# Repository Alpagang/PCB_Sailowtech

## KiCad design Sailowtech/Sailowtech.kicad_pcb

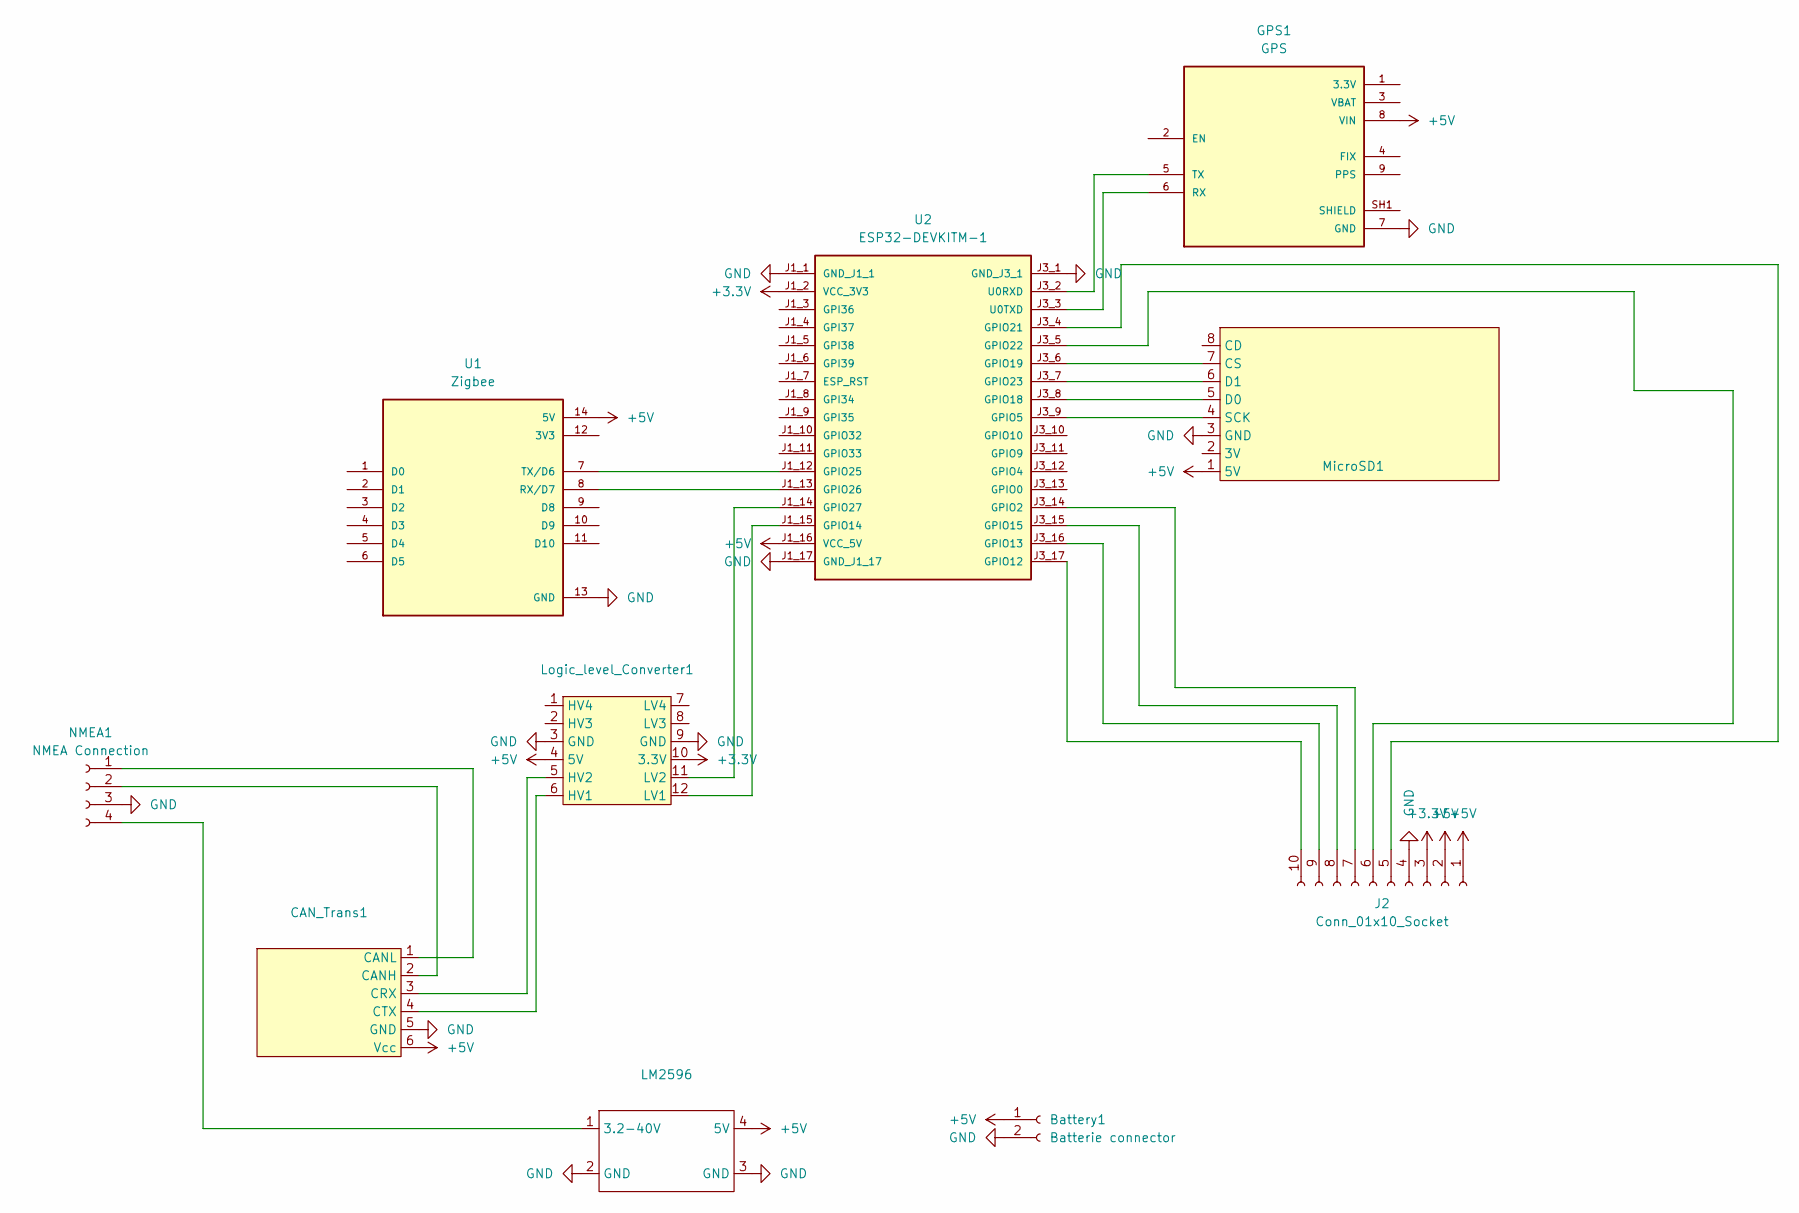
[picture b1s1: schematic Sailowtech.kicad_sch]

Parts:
Battery1: Batterie connector; PhoenixContact_MCV_1,5_2-G-3.5_1x02_P3.50mm_Vertical
CAN_Trans1: MCP - Canbus
GPS1: GPS; XCVR_746; PARTREV 2022-12-01; DigiKey_Part_Number 1528-1153-ND
J2: Conn_01x10_Socket; PinHeader_1x10_P2.54mm_Vertical
LM2596: Transformer 16V to 5V
Logic_level_Converter1: Logic_level_converter
MicroSD1: SD Card holder
NMEA1: NMEA Connection; PhoenixContact_MCV_1,5_4-G-3.5_1x04_P3.50mm_Vertical
U1: Zigbee; MODULE_113991254; PARTREV v1.0; DigiKey_Part_Number 1597-113991254-ND
U2: ESP32-DEVKITM-1; MODULE_ESP32-DEVKITM-1; PARTREV 1.0; DigiKey_Part_Number 1965-ESP32-DEVKITM-1-ND

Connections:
+3.3V: J2.3, Logic_level_Converter1.10 (3.3V), U2.J1_2 (VCC_3V3)
+5V: Battery1.1, CAN_Trans1.6 (Vcc), GPS1.8 (VIN), J2.1, J2.2, LM2596.4 (5V), Logic_level_Converter1.4 (5V), MicroSD1.1 (5V), U1.14 (5V), U2.J1_16 (VCC_5V)
GND: Battery1.2, CAN_Trans1.5 (GND), GPS1.7 (GND), J2.4, LM2596.2 (GND), LM2596.3 (GND), Logic_level_Converter1.3 (GND), Logic_level_Converter1.9 (GND), MicroSD1.3 (GND), NMEA1.3, U1.13 (GND), U2.J1_1 (GND_J1_1), U2.J1_17 (GND_J1_17), U2.J3_1 (GND_J3_1)
unnamed: CAN_Trans1.2 (CANH), NMEA1.2
unnamed: CAN_Trans1.1 (CANL), NMEA1.1
unnamed: CAN_Trans1.3 (CRX), Logic_level_Converter1.5 (HV2)
unnamed: CAN_Trans1.4 (CTX), Logic_level_Converter1.6 (HV1)
unnamed: GPS1.6 (RX), U2.J3_3 (U0TXD)
unnamed: GPS1.SH1 (SHIELD), GPS1.SH2 (SHIELD)
unnamed: GPS1.5 (TX), U2.J3_2 (U0RXD)
unnamed: J2.5, U2.J3_4 (GPIO21)
unnamed: J2.6, U2.J3_5 (GPIO22)
unnamed: J2.7, U2.J3_14 (GPIO2)
unnamed: J2.8, U2.J3_15 (GPIO15)
unnamed: J2.9, U2.J3_16 (GPIO13)
unnamed: J2.10, U2.J3_17 (GPIO12)
unnamed: LM2596.1 (3.2-40V), NMEA1.4
unnamed: Logic_level_Converter1.12 (LV1), U2.J1_15 (GPIO14)
unnamed: Logic_level_Converter1.11 (LV2), U2.J1_14 (GPIO27)
unnamed: MicroSD1.7 (CS), U2.J3_6 (GPIO19)
unnamed: MicroSD1.5 (D0), U2.J3_8 (GPIO18)
unnamed: MicroSD1.6 (D1), U2.J3_7 (GPIO23)
unnamed: MicroSD1.4 (SCK), U2.J3_9 (GPIO5)
unnamed: U1.8 (RX/D7), U2.J1_13 (GPIO26)
unnamed: U1.7 (TX/D6), U2.J1_12 (GPIO25)

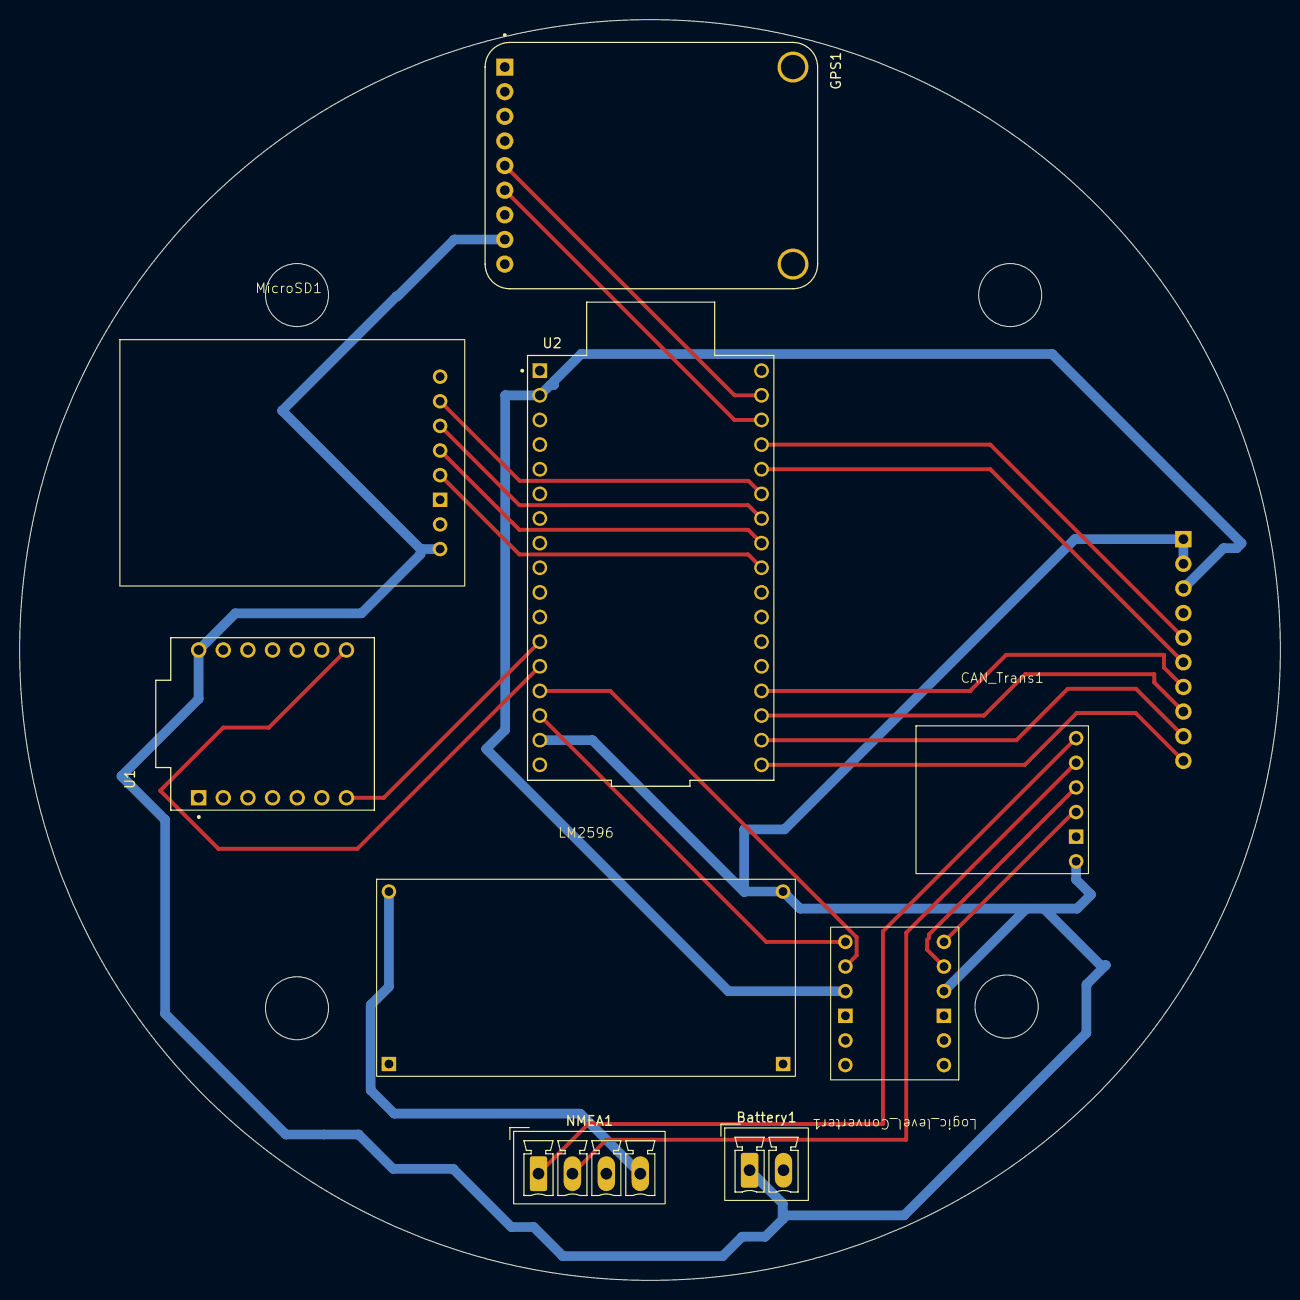
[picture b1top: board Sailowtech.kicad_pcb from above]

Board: 2 copper layers, 130.0 x 130.0 mm, 10 parts (1 on the bottom side), 25 nets.

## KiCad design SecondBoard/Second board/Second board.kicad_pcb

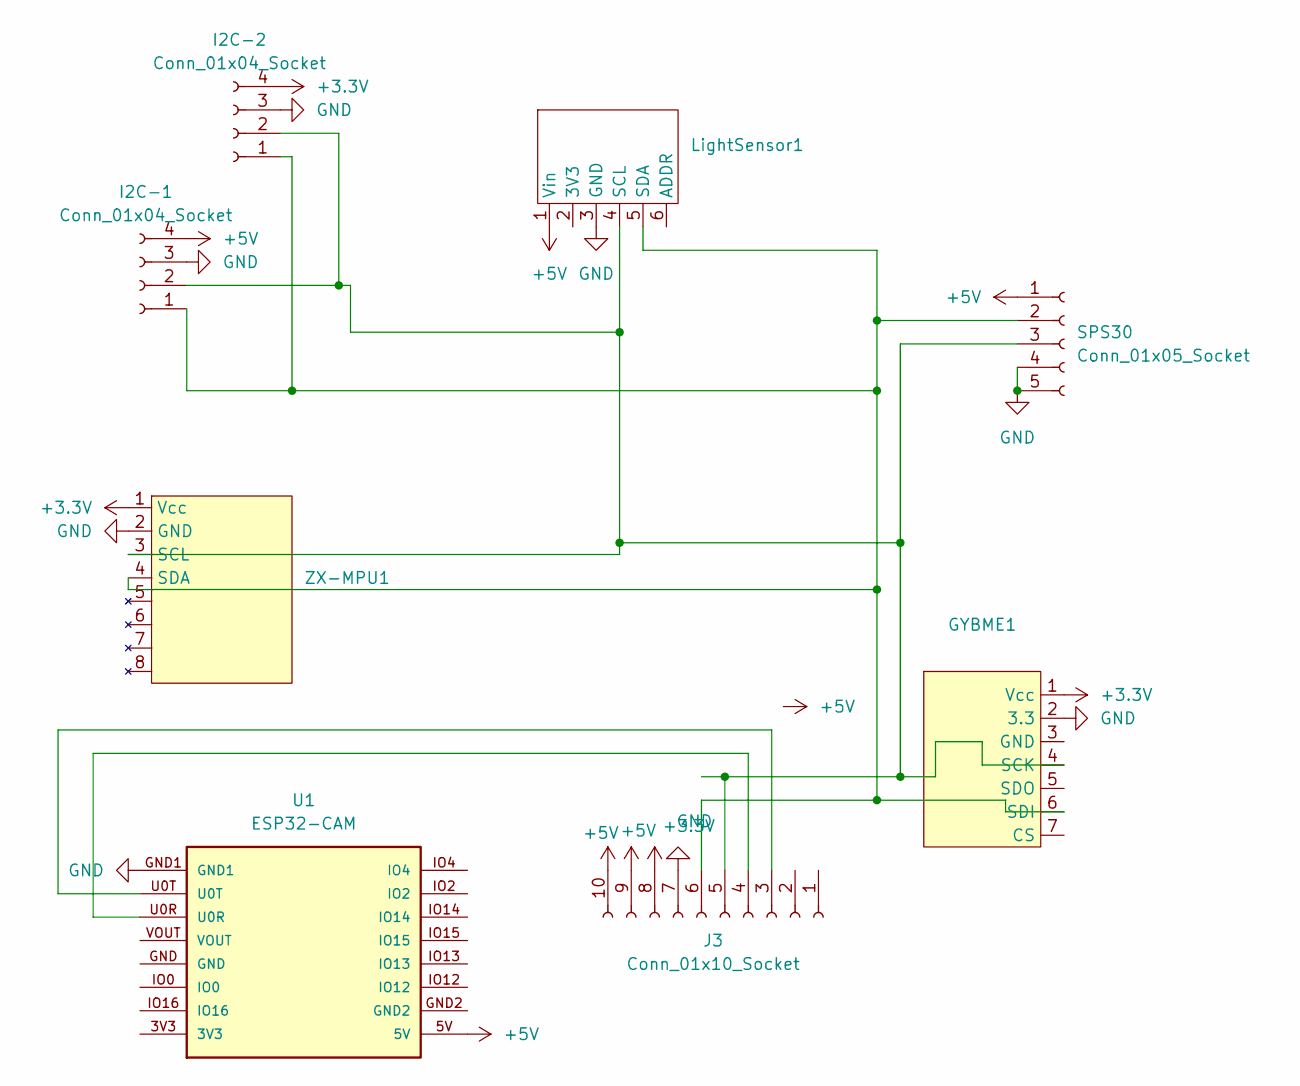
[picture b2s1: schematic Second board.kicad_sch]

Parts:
GYBME1: Sans titre
I2C-1, I2C-2: Conn_01x04_Socket; JST_XH_B4B-XH-AM_1x04_P2.50mm_Vertical
J3: Conn_01x10_Socket; PinSocket_1x10_P2.54mm_Vertical
LightSensor1: BH1750
SPS30: Conn_01x05_Socket; TerminalBlock_Phoenix_MKDS-1,5-5_1x05_P5.00mm_Horizontal
U1: ESP32-CAM
ZX-MPU1: ZX-MPU6050

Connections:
+3.3V: GYBME1.1 (Vcc), I2C-2.4, J3.8, ZX-MPU1.1 (Vcc)
+5V: I2C-1.4, J3.9, J3.10, LightSensor1.1 (Vin), SPS30.1, U1.5V
GND: GYBME1.2 (3.3), I2C-1.3, I2C-2.3, J3.7, LightSensor1.3 (GND), SPS30.4, SPS30.5, U1.GND1, ZX-MPU1.2 (GND)
unnamed: GYBME1.4 (SCK), I2C-1.2, I2C-2.2, J3.5, LightSensor1.4 (SCL), SPS30.3, ZX-MPU1.3 (SCL)
unnamed: GYBME1.6 (SDI), I2C-1.1, I2C-2.1, J3.6, LightSensor1.5 (SDA), SPS30.2, ZX-MPU1.4 (SDA)
unnamed: J3.3, U1.U0T
unnamed: J3.4, U1.U0R

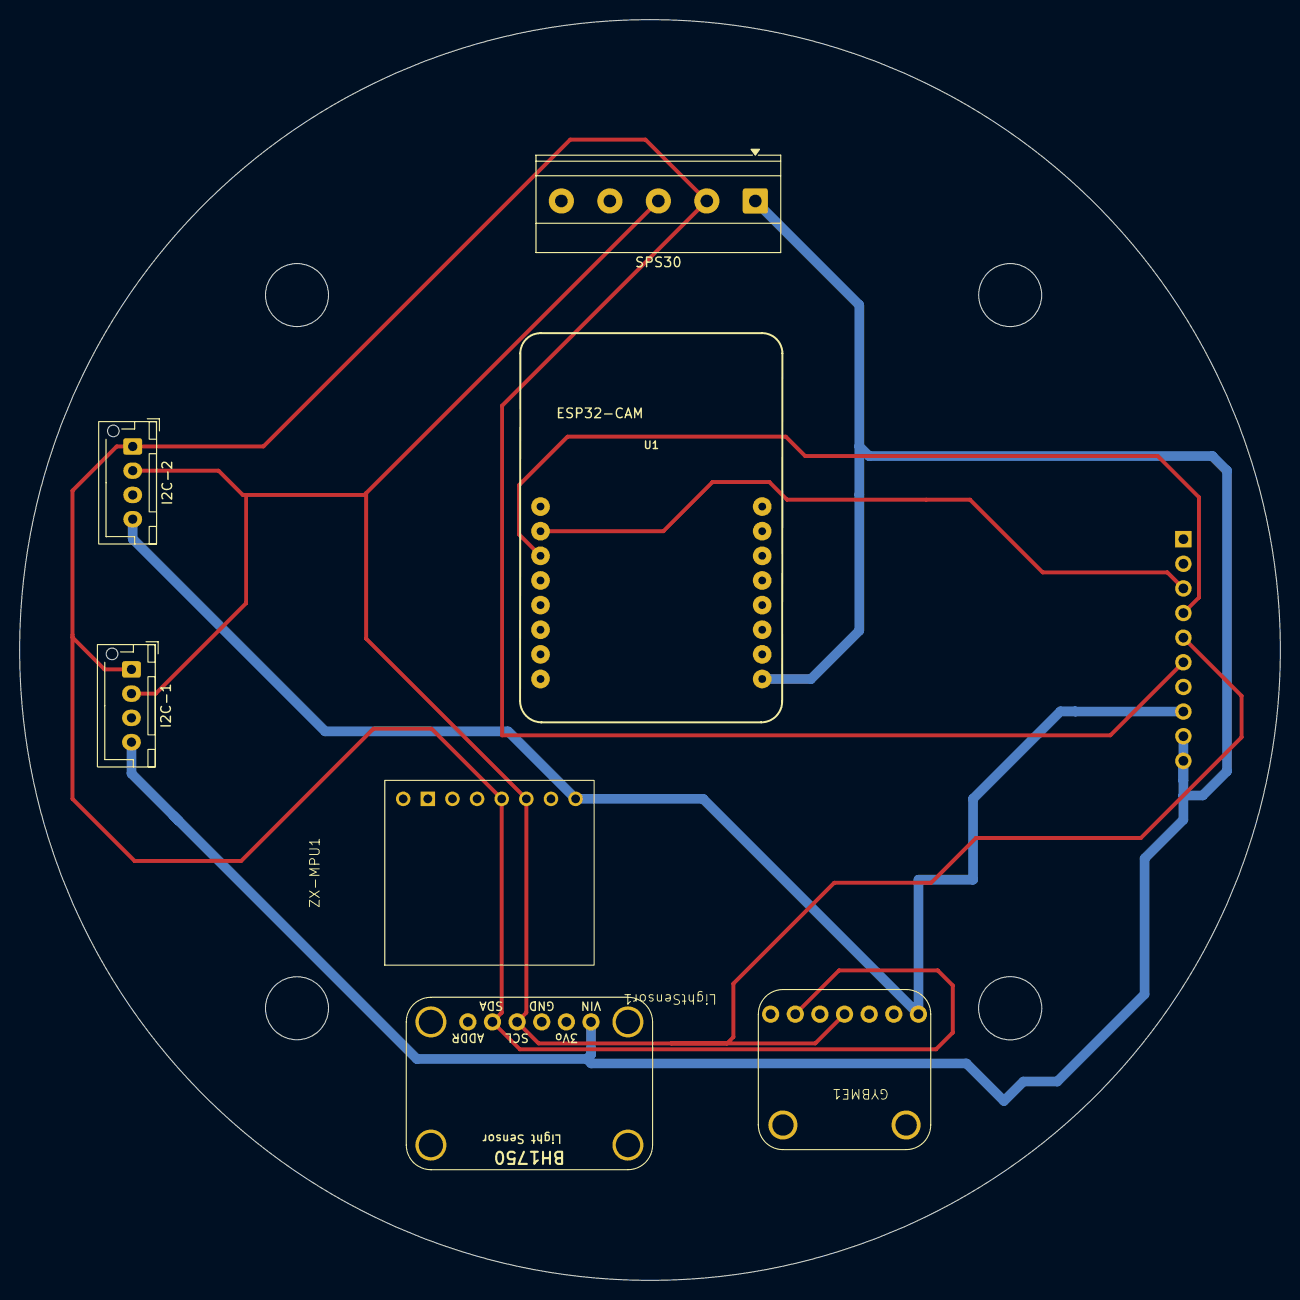
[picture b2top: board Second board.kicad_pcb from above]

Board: 2 copper layers, 130.0 x 130.0 mm, 8 parts (1 on the bottom side), 7 nets.

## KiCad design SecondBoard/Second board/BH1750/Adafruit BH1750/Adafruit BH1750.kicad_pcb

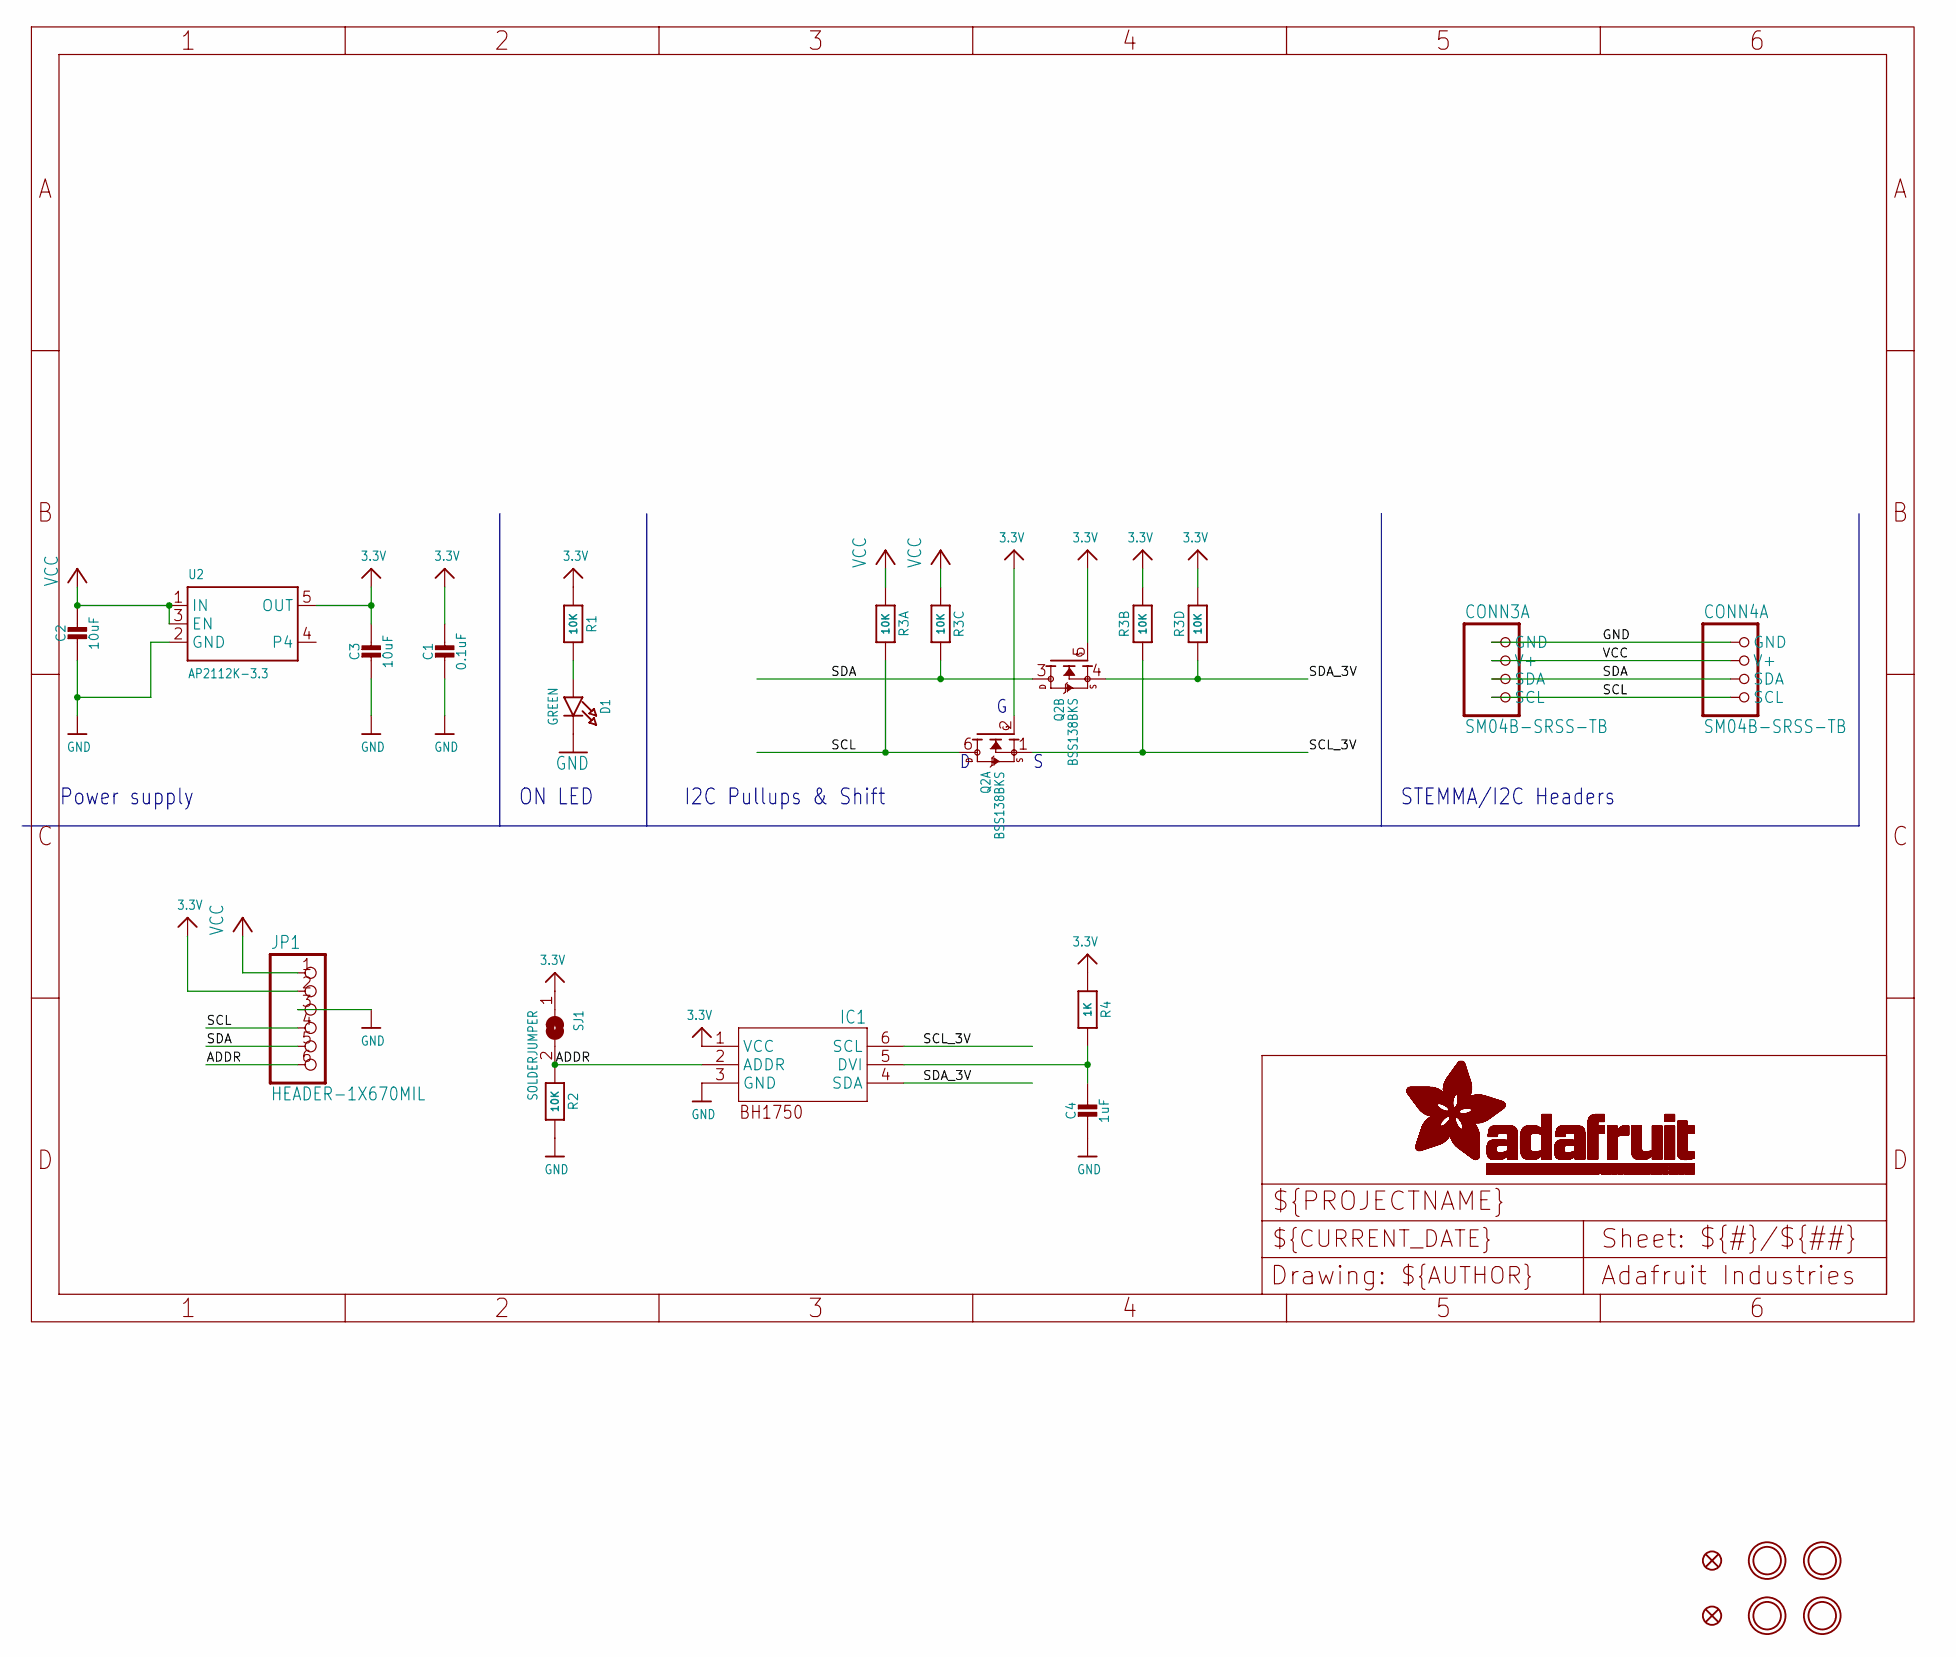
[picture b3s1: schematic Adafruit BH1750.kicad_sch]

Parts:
C1: 0.1uF; 0603-NO
C2, C3: 10uF; 0805-NO
C4: 1uF; 0603-NO
CONN3, CONN4: SM04B-SRSS-TB; JST_SH4
D1: GREEN; CHIPLED_0603_NOOUTLINE
FID3, FID4: FIDUCIAL_1MM
IC1: BH1750; WSOF-6
JP1: HEADER-1X670MIL; 1X06_ROUND_70
Q2: BSS138BKS; SOT363
R1, R2: 10K; 0603-NO
R3: 10K; RESPACK_4X0603
R4: 1K; 0603-NO
SJ1: SOLDERJUMPER; SOLDERJUMPER_ARROW_NOPASTE
U2: AP2112K-3.3; SOT23-5
U$1, U$17, U$19, U$21: MOUNTINGHOLE2.5; MOUNTINGHOLE_2.5_PLATED

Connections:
3.3V: C1.1, C3.1, IC1.1 (VCC), JP1.2, Q2.2 (G), Q2.5 (G), R1.1, R3.2 (1), R3.4 (1), R4.1, SJ1.1, U2.5 (OUT)
ADDR: IC1.2 (ADDR), JP1.6, R2.1, SJ1.2
GND: C1.2, C2.2, C3.2, C4.2, CONN3.1 (GND), CONN4.1 (GND), D1.C, IC1.3 (GND), JP1.3, R2.2, U2.2 (GND)
unnamed: D1.A, R1.2
unnamed: C4.1, IC1.5 (DVI), R4.2
SCL: CONN3.4 (SCL), CONN4.4 (SCL), JP1.4, Q2.6 (D), R3.8 (2)
SCL_3V: IC1.6 (SCL), Q2.1 (S), R3.7 (2)
SDA: CONN3.3 (SDA), CONN4.3 (SDA), JP1.5, Q2.3 (D), R3.6 (2)
SDA_3V: IC1.4 (SDA), Q2.4 (S), R3.5 (2)
VCC: C2.1, CONN3.2 (V+), CONN4.2 (V+), JP1.1, R3.1, R3.3 (1), U2.1 (IN), U2.3 (EN)

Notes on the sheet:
I2C Pullups & Shift
ON LED
STEMMA/I2C Headers
Power supply

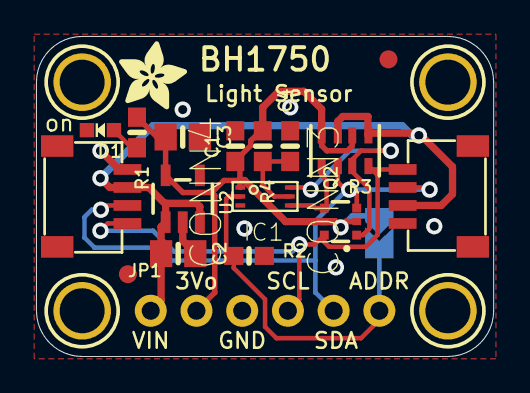
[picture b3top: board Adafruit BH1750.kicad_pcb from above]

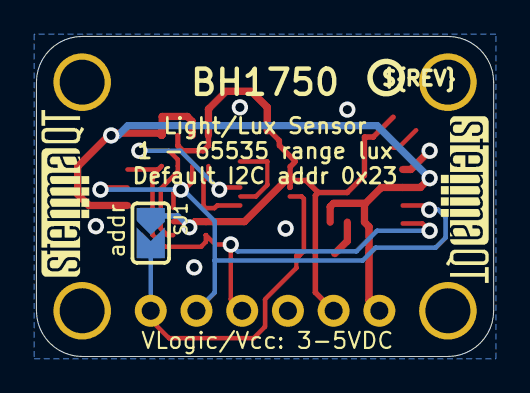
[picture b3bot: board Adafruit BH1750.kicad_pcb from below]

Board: 2 copper layers, 25.4 x 17.8 mm, 26 parts (4 on the bottom side), 10 nets.

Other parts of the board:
U$22: ADAFRUIT_3.5MM
U$25: PCBFEAT-REV-040
U$30, U$31: STEMMAQT

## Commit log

2026-03-23 Rond m190
2026-03-23 Rond m130
2026-03-23 SecondBoard Rond m130
2026-03-23 Plan de masse Update
2026-03-25 rajout gnd
2026-03-26 changement connecteur
2026-04-20 finished version
